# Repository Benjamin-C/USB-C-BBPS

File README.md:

# USBC-BBPS
A USBC-PD powered breadboard power supply with selectable voltage outputs. This lets you power your project with 3.3V and/or a voltage of your choice provided by a USBC Power Delivery capable power supply.

## Major Features
* A [CYPD3177-24LQXQT](https://www.infineon.com/cms/en/product/universal-serial-bus/usb-c-charging-port-controllers/ez-pd-barrel-connector-replacement-bcr/cypd3177-24lqxqt/) USBC PD Interface IC to supporting PD3.0 Revision 2.0 Version 1.3
* A [AP63203WU](https://www.mouser.com/ProductDetail/Diodes-Incorporated/AP63203WU-7?qs=u16ybLDytRZ1JqxbuLkMJw%3D%3D) 3.3V switching regulator to always have 3.3V available for microcontrollers
* An [LM339PWRG4](https://www.ti.com/product/LM339/part-details/LM339PWRG4) based voltage monitor
* 2x2 0.1" Pin headers spaced to fit standard solderless breadboards

## Ratings
* VBUS has a 1.5A polyfuse, so no more than 1.5A may be drawn between the VBUS output and 3.3V regulator (noting that the current drawn by the regulator from VBUS will be less than the current drawn on 3.3V).
* Do not feed power back into either 3.3V or VBUS. Doing so may kill the board or possibly the USB power supply
* Each side of the board has a maximum of 1A. This is not regulated on the board, so don't draw more than that.

## Configuration
### VBUS selection:
|      | SW3 | SW2 | SW1 |
|------|-----|-----|-----|
| 5V   |  A  |  A  |  A  |
| 9V   |  A  |  A  |  B  |
| 12V* |  A  |  B  |  A  |
| 15V  |  A  |  B  |  B  |
| 20V  |  B  |  x  |  x  |

\* 12V is an optional part of the USBC-PD spec, so many laptop chargers including most Apple ones do not support 12V.

### Output Voltage Selection
* Use the 3-pin jumpers on each side of the board to select the voltage output to that side of the breadboard.
* Each side can be independently selected to be 3.3V or VBUS.
* Only 1 VBUS voltage may be used at a time, but it may be used on both sides of the board.
* For any voltage over 5V, one or more of the output voltage monitoring LEDs will be lit. The output voltage is the highest value with a lit LED.
* Power will only be provided to the board once USBC-PD negotiations have completed and the desired voltage has been provided.

### Errors
* If the board is not able to negotiate at least the desired voltage from the upstream power supply, the outputs will be turned off and the fault LED will be turned on and power will be cut from the board.
* If the polyfuse is tripped, all lights on the board will turn off. To reset the polyfuse, turn disconnect power from the board, remove the cause of the over current event, and return power to the board.
* If there is a larger over current event, the protection in the USBC power supply may be triggered before the polyfuse reacts. To fix this, disconnect power from the board, remove the source of the nonrecurrent event, then reconnect power to the board.
* If the 3.3V light and voltage monitoring lights are blinking but the VBUS light is on, this is an indication that the 3.3V regulator may be damaged and require replacement.

## Assembly
* Mount the switch so that the switches are "on" when the switch is towards the bottom of the board and "off" when the switch is towards the top of the board. A "A" state is when the switch is down towards the bottom of the board (connected), and a "B" state is when the switch is towards the top of the board (disconnected)
* Be sure to securely solder the mounting tabs on the USBC connector to prevent damage to the board if the cable is pulled.

## More features!
* The 3 pin connector near the USBC connector exposes the I2C lines from the [CYPD3177-24LQXQT](https://www.infineon.com/cms/en/product/universal-serial-bus/usb-c-charging-port-controllers/ez-pd-barrel-connector-replacement-bcr/cypd3177-24lqxqt/) USBC PD Interface IC, and can be connected to a microcontroller for additional features.

## Design notes
This board was designed entirely by me based on the reference schematics for the utilized ICs.

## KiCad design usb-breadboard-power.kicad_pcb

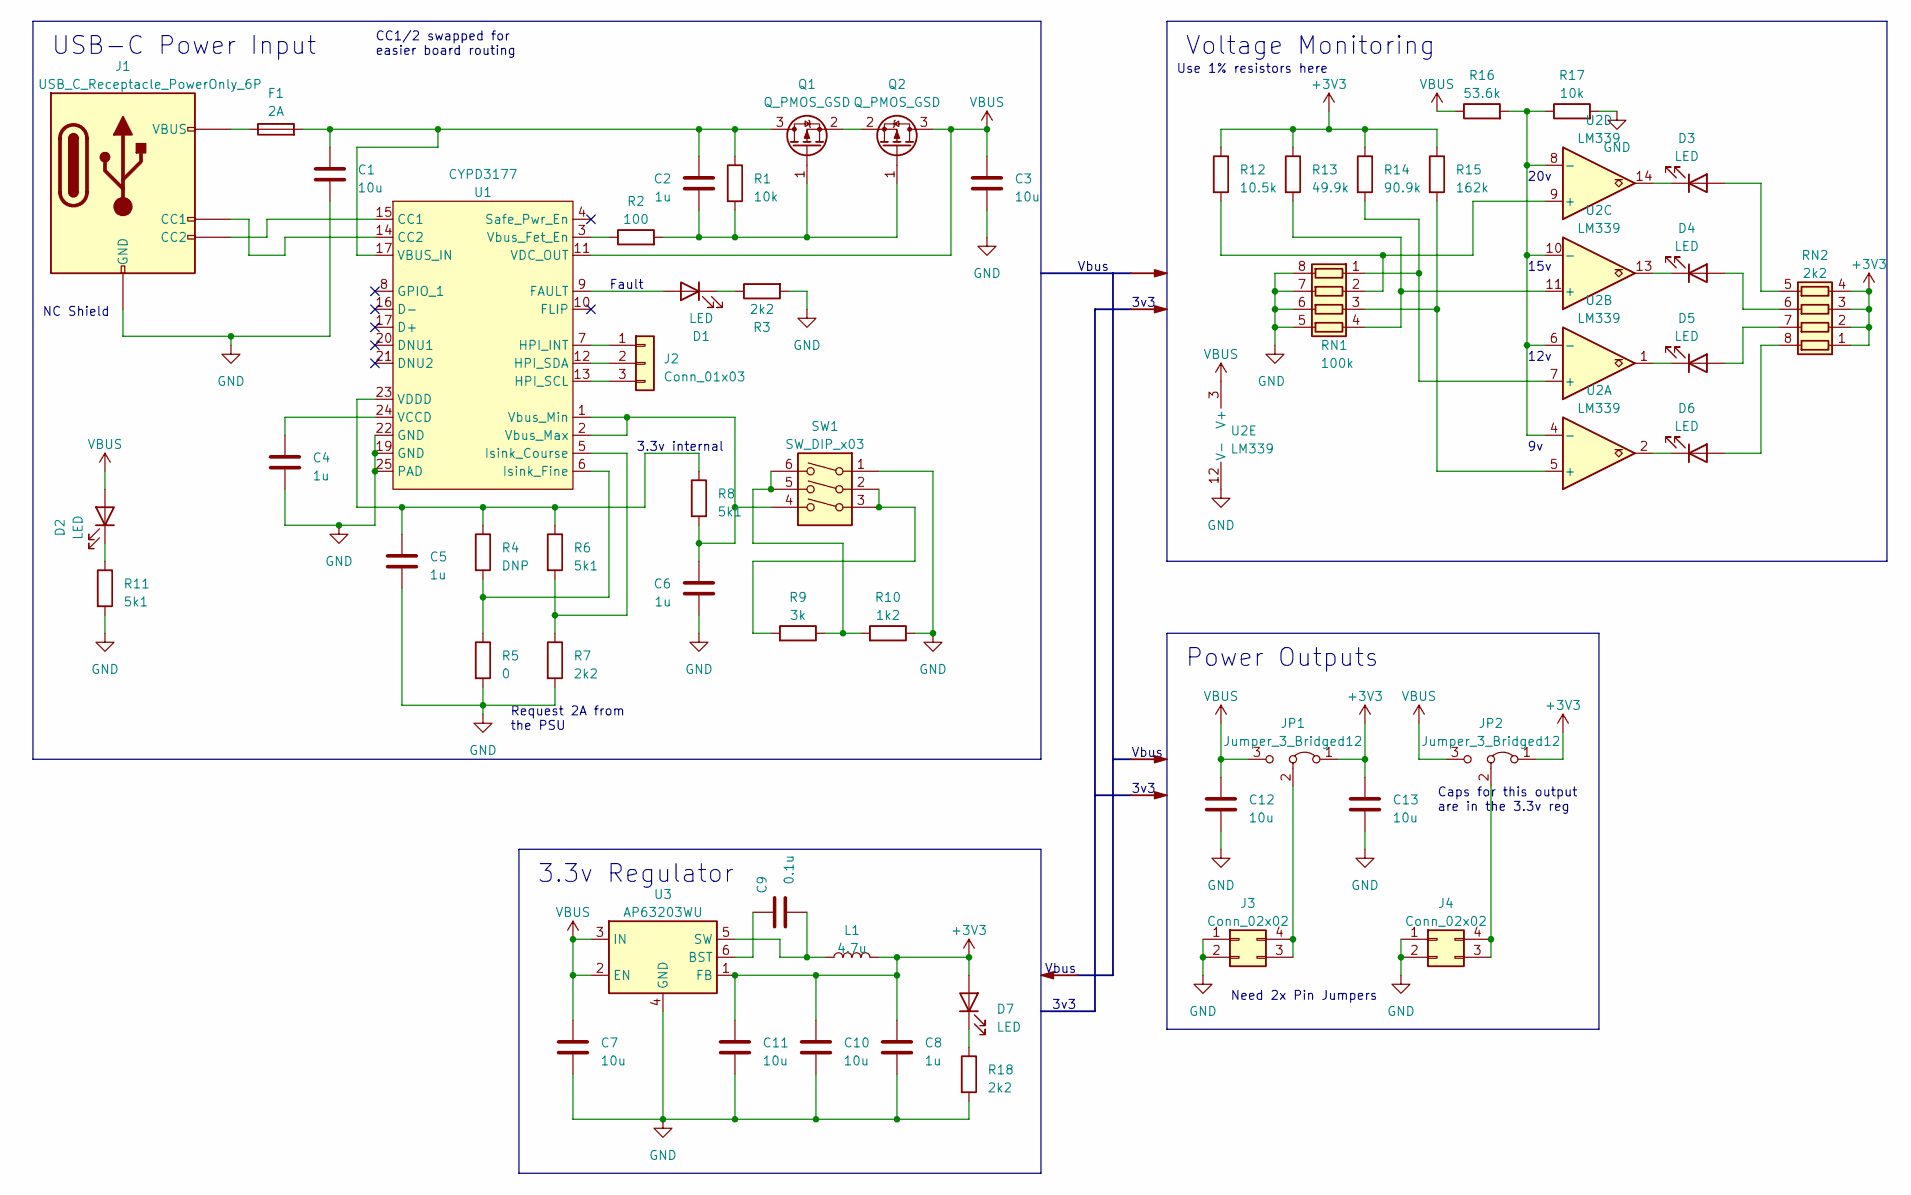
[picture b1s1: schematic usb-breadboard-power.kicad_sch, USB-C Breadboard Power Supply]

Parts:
C1: 10u; C_1206_3216Metric; MPN CL31A106KAHNNNE
C2, C4, C5, C6, C8: 1u; C_1206_3216Metric; MPN CL31B105KAHNNNE
C3, C7, C10, C11, C12, C13: 10u; C_1206_3216Metric; MPN CL31B105KAHNNNE
C9: 0.1u; C_1206_3216Metric; MPN-m CL31B104KBCNNNC
D1, D2, D3, D4, D5, D6, D7: LED; LED_1206_3216Metric; MPN LTST-C150GKT
F1: 2A; Fuse_1812_4532Metric; MPN-m 1812L150/24MR
J1: USB_C_Receptacle_PowerOnly_6P; J-Amphenol-USB-C; MPN 10164359-00011LF
J2: Conn_01x03; PinHeader_1x03_P2.54mm_Vertical_SMD_Pin1Left; MPN-m 10129380-903001ALF
J3, J4: Conn_02x02; PinHeader_2x02_P2.54mm_Vertical; MPN PH2-04-UA
JP1, JP2: Jumper_3_Bridged12; PinHeader_1x03_P2.54mm_Vertical_SMD_Pin1Left; MPN NREC003SABC-M30RC
L1: 4.7u; L_1210_3225Metric; MPN-m SRP3212A-4R7M
Q1, Q2: Q_PMOS_GSD; SOT-23-3; MPN-m DMP3099L-7
R1: 10k; R_1206_3216Metric; MPN-m CR1206-FX-1002ELF
R2: 100; R_1206_3216Metric; MPN RMCF1206JT100R
R3, R18: 2k2; R_1206_3216Metric; MPN RMCF1206JT2K20
R4: DNP; R_1206_3216Metric
R5: 0; R_1206_3216Metric; MPN-m CR1206-J/-000ELF
R6, R8, R11: 5k1; R_1206_3216Metric; MPN-m CR1206FX-5101ELF
R7: 2k2; R_1206_3216Metric; MPN-m CR1206-FX-2201ELF
R9: 3k; R_1206_3216Metric; MPN-m CR1206-FX-3001ELF
R10: 1k2; R_1206_3216Metric; MPN-m CR1206-FX-1201ELF
R12: 10.5k; R_1206_3216Metric; MPN RMCF1206ZT0R00
R13: 49.9k; R_1206_3216Metric; MPN RMCF1206FT36K5
R14: 90.9k; R_1206_3216Metric; MPN RMCF1206FT73K2
R15: 162k; R_1206_3216Metric; MPN RMCF1206FT137K
R16: 53.6k; R_1206_3216Metric; MPN RMCF1206FT536K
R17: 10k; R_1206_3216Metric; MPN RMCF1206FT100K
RN1: 100k; R_Array_Convex_4x1206; MPN TC164-FR-07100KL
RN2: 2k2; R_Array_Convex_4x1206; MPN TC164-FR-072K2L
SW1: SW_DIP_x03; SW_DIP_SPSTx03_Slide_6.7x9.18mm_W8.61mm_P2.54mm_LowProfile; MPN-m DS04-254-2-03BK-SMT
U1: CYPD3177; QFN-24-1EP_4x4mm_P0.5mm_EP2.8x2.8mm; MPN CYPD3177-24LQXQT
U2: LM339; TSSOP-14_4.4x5mm_P0.65mm; MPN LM339PWRG3
U3: AP63203WU; TSOT-23-6; MPN-m AP63203WU-7

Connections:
+3V3: C8.1, C10.1, C11.1, C13.1, D7.2 (A), JP1.1 (A), JP2.1 (A), L1.2, R12.1, R13.1, R14.1, R15.1, RN2.1 (R1.1), RN2.2 (R2.1), RN2.3 (R3.1), RN2.4 (R4.1), U3.1 (FB)
GND: C1.2, C3.2, C4.2, C5.2, C6.2, C7.2, C8.2, C10.2, C11.2, C12.2, C13.2, J1.A12 (GND), J1.B12 (GND), J3.1, J3.2, J4.1, J4.2, R3.2, R5.2, R7.2, R10.1, R11.2, R17.2, R18.2, RN1.5 (R4.2), RN1.6 (R3.2), RN1.7 (R2.2), RN1.8 (R1.2), SW1.1, U1.19 (GND), U1.22 (GND), U1.25 (PAD), U2.12 (V-), U3.4 (GND)
unnamed: D1.2 (A), U1.9 (FAULT)
unnamed: D1.1 (K), R3.1
unnamed: D2.1 (K), R11.1
unnamed: D3.2 (A), RN2.5 (R4.2)
unnamed: D3.1 (K), U2.14
unnamed: D4.2 (A), RN2.6 (R3.2)
unnamed: D4.1 (K), U2.13
unnamed: D5.2 (A), RN2.7 (R2.2)
unnamed: D5.1 (K), U2.1
unnamed: D6.2 (A), RN2.8 (R1.2)
unnamed: D6.1 (K), U2.2
unnamed: D7.1 (K), R18.1
unnamed: F1.1, J1.A9 (VBUS), J1.B9 (VBUS)
unnamed: J1.A5 (CC1), U1.14 (CC2)
unnamed: J1.B5 (CC2), U1.15 (CC1)
unnamed: J2.1, U1.7 (HPI_INT)
unnamed: J2.2, U1.12 (HPI_SDA)
unnamed: J2.3, U1.13 (HPI_SCL)
unnamed: J3.3, J3.4, JP1.2 (C)
unnamed: J4.3, J4.4, JP2.2 (C)
unnamed: C1.1, C2.1, F1.2, Q1.3 (D), R1.1, U1.17 (D+), U1.18 (VBUS_IN)
unnamed: C2.2, Q1.1 (G), Q2.1 (G), R1.2, R2.2
unnamed: Q1.2 (S), Q2.2 (S)
unnamed: R9.2, SW1.2, SW1.3
unnamed: R9.1, R10.2, SW1.5, SW1.6
unnamed: R14.2, RN1.1 (R1.1), U2.7 (+)
unnamed: R12.2, RN1.2 (R2.1), U2.9 (+)
unnamed: R15.2, RN1.3 (R3.1), U2.5 (+)
unnamed: R13.2, RN1.4 (R4.1), U2.11 (+)
unnamed: R6.2, R7.1, U1.5 (Isink_Course)
unnamed: R4.2, R5.1, U1.6 (Isink_Fine)
unnamed: C4.1, U1.24 (VCCD)
unnamed: C5.1, R4.1, R6.1, R8.1, U1.23 (VDDD)
unnamed: R2.1, U1.3 (Vbus_Fet_En)
unnamed: C6.1, R8.2, SW1.4, U1.1 (Vbus_Min), U1.2 (Vbus_Max)
unnamed: R16.2, R17.1, U2.4 (-), U2.6 (-), U2.8 (-), U2.10 (-)
unnamed: C9.2, U3.6 (BST)
unnamed: C9.1, L1.1, U3.5 (SW)
VBUS: C3.1, C7.1, C12.1, D2.2 (A), JP1.3 (B), JP2.3 (B), Q2.3 (D), R16.1, U1.11 (VDC_OUT), U2.3 (V+), U3.2 (EN), U3.3 (IN)

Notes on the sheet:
Power Outputs
3v3
Use 1% resistors here
12v
USB-C Power Input
NC Shield
3.3v internal
Request 2A from the PSU
Vbus
15v
CC1/2 swapped for easier board routing
Voltage Monitoring
20v
Caps for this output are in the 3.3v reg
Need 2x Pin Jumpers
3.3v Regulator
Fault

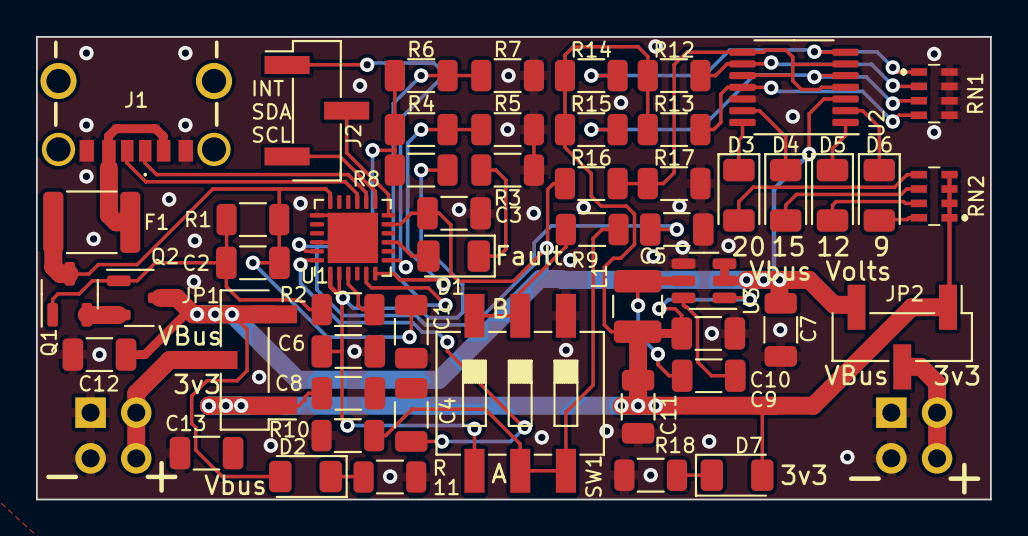
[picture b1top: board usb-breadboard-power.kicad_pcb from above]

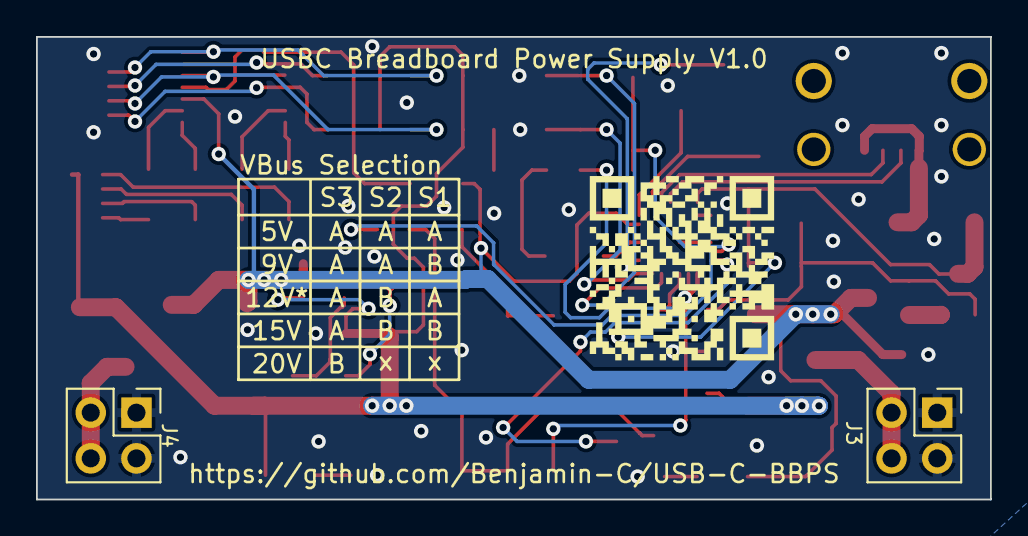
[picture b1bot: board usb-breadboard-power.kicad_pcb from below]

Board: 2 copper layers, 53.0 x 25.7 mm, 54 parts (2 on the bottom side), 41 nets.

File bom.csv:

USB-C Powered Breadboard Power Supply V1.0,,,,,
All parts ordered from Mouser,,,,,
Thu 08 Jun 2023,,,,,
Component Count:,56,,,,
Item,Qty,Reference(s),Value,DPN,MPN
1,7,"C1, C3, C7, C10, C11, C12, C13",10u,187-CL31A106MBHNNNE,CL31A106MBHNNNE
2,5,"C2, C4, C5, C6, C8",1u,187-CL31B105KBHNFNE,CL31B105KBHNFNE
3,1,C9,0.1u,187-CL31B104KBCNNND,CL31B104KBCNNND
4,7,"D1, D2, D3, D4, D5, D6, D7",LED,710-156120RS75000 ,156120RS75000 
5,1,F1,2A,576-1812L150/24MR ,1812L150/24MR
6,1,J1,USB_C_Receptacle_PowerOnly_6P,649-10164359-00011LF,10164359-00011LF 
7,1,J2,DNP, 649-1012938090301ALF,10129380-903001ALF
8,2,"J3, J4",Conn_02x02,649-1012938190403BLF,10129381-904003BLF 
9,2,"JP1, JP2",Jumper_3_Bridged12,649-1012938090301ALF ,10129380-903001ALF
10,2,"JS1, JS2",~,855-M7581-05,M7581-05
11,1,L1,4.7u,652-SRP3212A-4R7M,SRP3212A-4R7M 
12,2,"Q1, Q2",Q_PMOS_GSD,621-DMP3099L-7,DMP3099L-7
13,2,"R1, R17",10k,652-CR1206FX-1002ELF,CR1206-FX-1002ELF
14,1,R2,100,652-CR1206FX-1000ELF,CR1206-FX-1000ELF
15,3,"R3, R7, R18",2k2,652-CR1206FX-2201ELF,CR1206-FX-2201ELF
16,1,R4,DNP,,
17,1,R5,0,652-CR1206-J/-000ELF ,CR1206-J/-000ELF 
18,3,"R6, R8, R11",5k1,652-CR1206FX-5101ELF,CR1206FX-5101ELF
19,1,R9,3k,652-CR1206FX-3001ELF,CR1206-FX-3001ELF
20,1,R10,1k2,652-CR1206FX-1201ELF,CR1206-FX-1201ELF
21,1,R12,10.5k,652-CR1206FX-1052ELF,CR1206FX-1052ELF
22,1,R13,49.9k,652-CR1206FX-4992ELF,CR1206FX-4992ELF
23,1,R14,90.9k,652-CR1206FX-9092ELF,CR1206FX-9092ELF
24,1,R15,162k,652-CR1206FX-1623ELF,CR1206FX-1623ELF
25,1,R16,53.6k,652-CR1206FX-5362ELF,CR1206-FX-5362ELF
26,1,RN1,100k,603-TC164-FR-07100KL,TC164-FR-07100KL
27,1,RN2,2k2,603-YC164-FR-072K2L,YC164-FR-072K2L
28,1,SW1,SW_DIP_x03,490-DS04254203BK-SMT ,DS04-254-2-03BK-SMT 
29,1,U1,CYPD3177,727-CYPD3177-24LQXQT,CYPD3177-24LQXQT
30,1,U2,LM339,595-LM339PWRG4,LM339PWRG4 
31,1,U3,AP63203WU,621-AP63203WU-7,AP63203WU-7

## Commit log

2023-06-08 Cleaned up repo
2023-06-08 Updated Mouser BOM
2023-06-08 Fixed switching reg layout
2023-06-08 Moved voltage LED refdes out from under diodes
2023-06-08 Added jumper shunts to BOM
2023-06-08 Swapped IC to one that supports 12v
2023-06-08 More small fixes
2023-06-08 Fixed BOM errors
2023-06-08 Fixed issues discovered while building first run
2023-06-08 Confirmed BOM
2023-06-08 init
2023-06-08 Cleaned up schematic and added Vbus LED
2023-06-08 Updated gitignore and added fuse
2023-06-08 Updated documentation
2023-06-08 Added board fab files
2023-06-08 created VBUS selection guide
    made an SVG of the table showing how to select vbus voltage and added it to the "graphics" folder
2023-06-09 Adding renders
2023-06-09 Added info to back of board
2023-06-09 More details in README
